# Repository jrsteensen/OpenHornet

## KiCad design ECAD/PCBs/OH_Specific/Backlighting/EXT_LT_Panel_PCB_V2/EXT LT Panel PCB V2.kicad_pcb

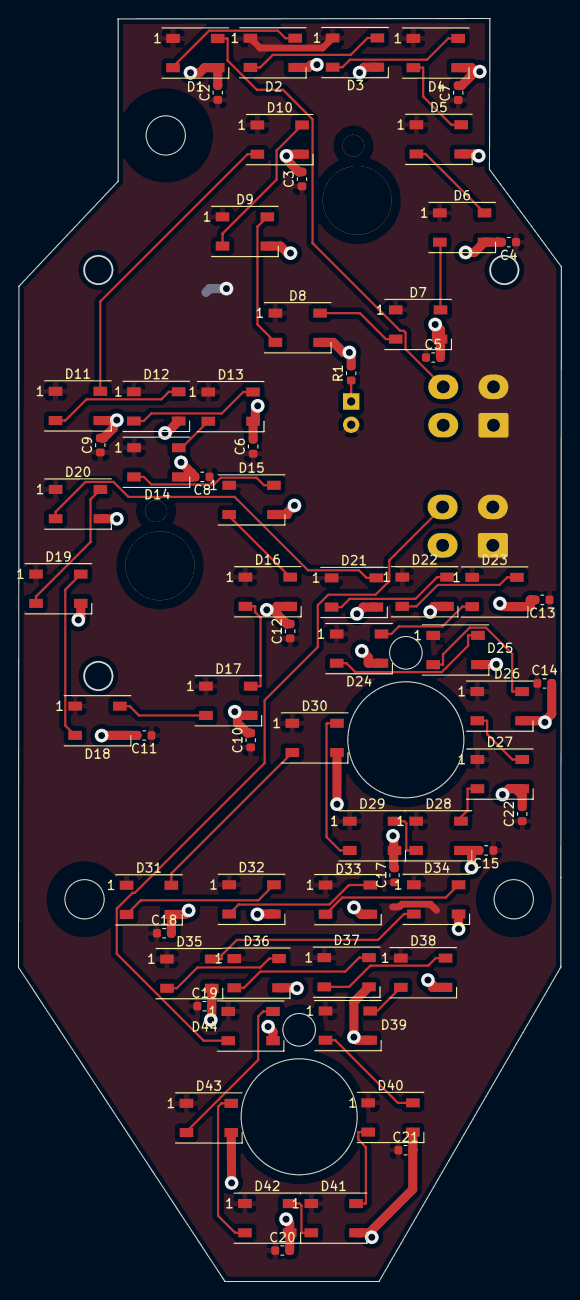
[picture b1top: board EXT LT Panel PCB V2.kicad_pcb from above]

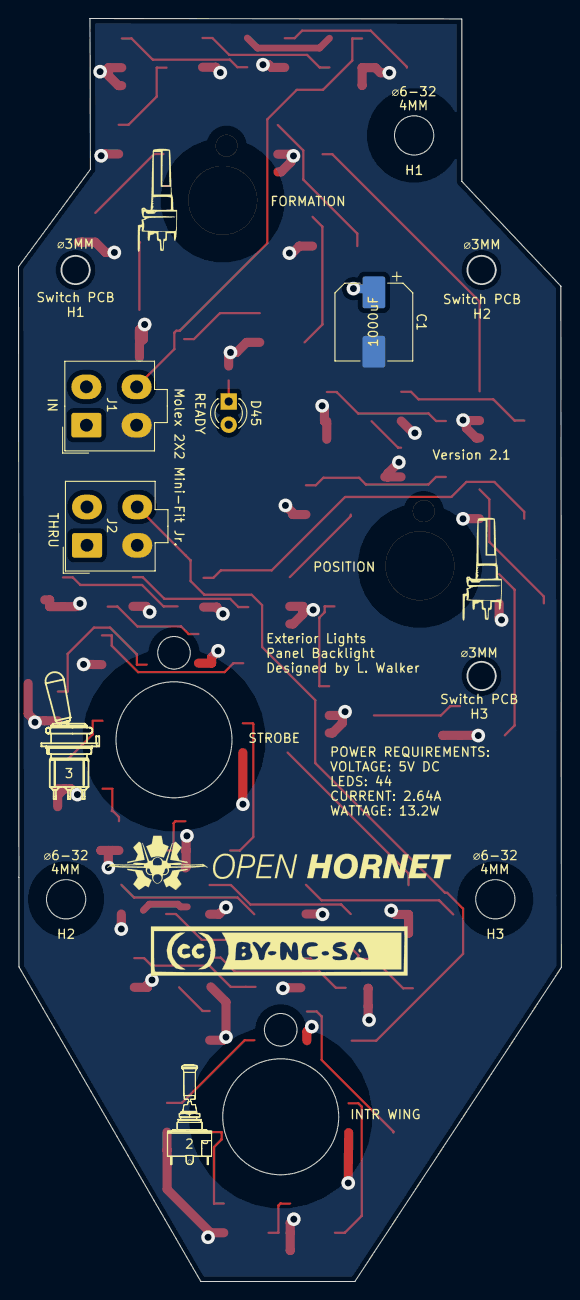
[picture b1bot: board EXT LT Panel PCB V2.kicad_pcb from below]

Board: 2 copper layers, 59.4 x 138.3 mm, 80 parts (7 on the bottom side), 48 nets.

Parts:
1, 2: BR10K_Pot_11mm_x_11mm
3, 4: 100SPX_Toggle_13mm_x_18mm
5, 6, 7: OH_Panel_Fastner_Keepout; OH_Panel_6-32_PHS
C1: C_Polarized; CP_Elec_8x10
C2, C3, C4, C5, C6, C7, C8, C9, C10, C11, C12, C13, C14, C15, C17, C18, C19, C20, C21, C22: C; C_0603_1608Metric
D1, D2, D3, D4, D5, D6, D7, D8, D9, D10, D11, D12, D13, D14, D15, D16, D17, D18, D19, D20, D21, D22, D23, D24, D25, D26, D27, D28, D29, D30, D31, D32, D33, D34, D35, D36, D37, D38, D39, D40, D41, D42, D43, D44: WS2812B; LED_WS2812B_PLCC4_5.0x5.0mm_P3.2mm
D45: LED; LED_D3.0mm
G1, G2: LOGO; BR10KPot
G3: LOGO; 100SpxToggle
G4: LOGO; S2ALToggle
J1, J2: Conn_01x04_Female; Molex_Mini-Fit_Jr_5566-04A_2x02_P4.20mm_Vertical
R1: R; R_0603_1608Metric

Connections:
/DATAIN: D1.4, J1.4
/DATAOUT: D44.2, J2.4
/LED+5V: C1.1, C2.1, C3.1, C4.1, C5.1, C6.1, C7.1, C8.1, C9.1, C10.1, C11.1, C12.1, C13.1, C14.1, C15.1, C17.1, C18.1, C19.1, C20.1, C21.1, C22.1, D1.1, D2.1, D3.1, D4.1, D5.1, D6.1, D7.1, D8.1, D9.1, D10.1, D11.1, D12.1, D13.1, D14.1, D15.1, D16.1, D17.1, D18.1, D19.1, D20.1, D21.1, D22.1, D23.1, D24.1, D25.1, D26.1, D27.1, D28.1, D29.1, D30.1, D31.1, D32.1, D33.1, D34.1, D35.1, D36.1, D37.1, D38.1, D39.1, D40.1, D41.1, D42.1, D43.1, D44.1, D45.2, J1.1, J1.2, J2.1, J2.2
/LEDGND: C1.2, C2.2, C3.2, C4.2, C5.2, C6.2, C7.2, C8.2, C9.2, C10.2, C11.2, C12.2, C13.2, C14.2, C15.2, C17.2, C18.2, C19.2, C20.2, C21.2, C22.2, D1.3, D2.3, D3.3, D4.3, D5.3, D6.3, D7.3, D8.3, D9.3, D10.3, D11.3, D12.3, D13.3, D14.3, D15.3, D16.3, D17.3, D18.3, D19.3, D20.3, D21.3, D22.3, D23.3, D24.3, D25.3, D26.3, D27.3, D28.3, D29.3, D30.3, D31.3, D32.3, D33.3, D34.3, D35.3, D36.3, D37.3, D38.3, D39.3, D40.3, D41.3, D42.3, D43.3, D44.3, J1.3, J2.3, R1.2
unnamed: D1.2, D2.4
unnamed: D2.2, D3.4
unnamed: D3.2, D4.4
unnamed: D4.2, D5.4
unnamed: D5.2, D6.4
unnamed: D6.2, D7.4
unnamed: D7.2, D8.4
unnamed: D8.2, D9.4
unnamed: D10.2, D11.4
unnamed: D9.2, D10.4
unnamed: D11.2, D12.4
unnamed: D12.2, D13.4
unnamed: D13.2, D14.4
unnamed: D14.2, D15.4
unnamed: D15.2, D16.4
unnamed: D16.2, D17.4
unnamed: D17.2, D18.4
unnamed: D18.2, D19.4
unnamed: D19.2, D20.4
unnamed: D20.2, D21.4
unnamed: D21.2, D22.4
unnamed: D22.2, D23.4
unnamed: D23.2, D24.4
unnamed: D24.2, D25.4
unnamed: D25.2, D26.4
unnamed: D26.2, D27.4
unnamed: D27.2, D28.4
unnamed: D28.2, D29.4
unnamed: D29.2, D30.4
unnamed: D30.2, D31.4
unnamed: D31.2, D32.4
unnamed: D32.2, D33.4
unnamed: D33.2, D34.4
unnamed: D34.2, D35.4
unnamed: D35.2, D36.4
unnamed: D36.2, D37.4
unnamed: D37.2, D38.4
unnamed: D38.2, D39.4
unnamed: D39.2, D40.4
unnamed: D40.2, D41.4
unnamed: D41.2, D42.4
unnamed: D42.2, D43.4
unnamed: D43.2, D44.4
unnamed: D45.1, R1.1
